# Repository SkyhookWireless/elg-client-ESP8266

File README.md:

# elg-client-demo
ELG Client Demo Space

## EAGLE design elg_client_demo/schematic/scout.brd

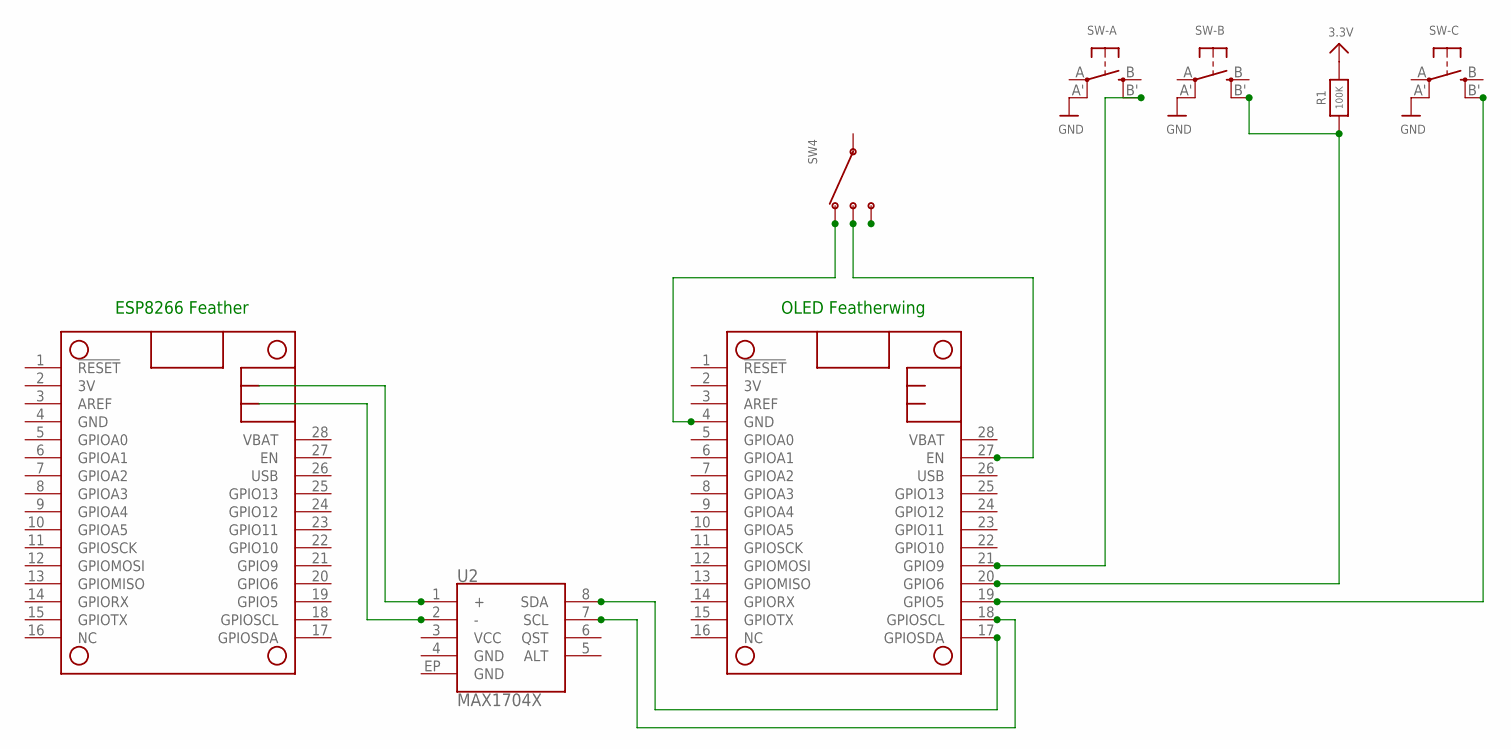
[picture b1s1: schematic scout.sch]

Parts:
MS1, MS2: MICROBUILDER_FEATHERWING_NODIM; MICROBUILDER_FEATHERWING_DIM
R1: 100K; MICROBUILDER_0603-MINI
SW4: CSS-1310TB; JSM07011
SW-A: MICROBUILDER_SWITCH_TACT_SMTKMT0; MICROBUILDER_BTN_KMT0
SW-B: MICROBUILDER_SWITCH_TACT_SMTKMT0; MICROBUILDER_BTN_KMT0
SW-C: MICROBUILDER_SWITCH_TACT_SMTKMT0; MICROBUILDER_BTN_KMT0
U2: MAX1704X; SPARKFUN_TDFN-8

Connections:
3.3V: R1.2
GND: MS2.4 (GND), SW-A.A' (P1), SW-B.A' (P1), SW-C.A' (P1)
unnamed: MS1.21 (GPIO9), SW-A.B' (S1)
unnamed: MS1.20 (GPIO6), R1.1, SW-B.B' (S1)
unnamed: MS1.19 (GPIO5), SW-C.B' (S1)
unnamed: MS1.4 (GND), SW4.4 (3)
unnamed: MS1.27 (EN), SW4.2
unnamed: MS1.17 (GPIOSDA), U2.8 (SDA)
unnamed: MS1.18 (GPIOSCL), U2.7 (SCL)

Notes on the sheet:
ESP8266 Feather
OLED Featherwing

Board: 2 copper layers, 8 parts (0 on the bottom side), 8 nets, no tracks yet.

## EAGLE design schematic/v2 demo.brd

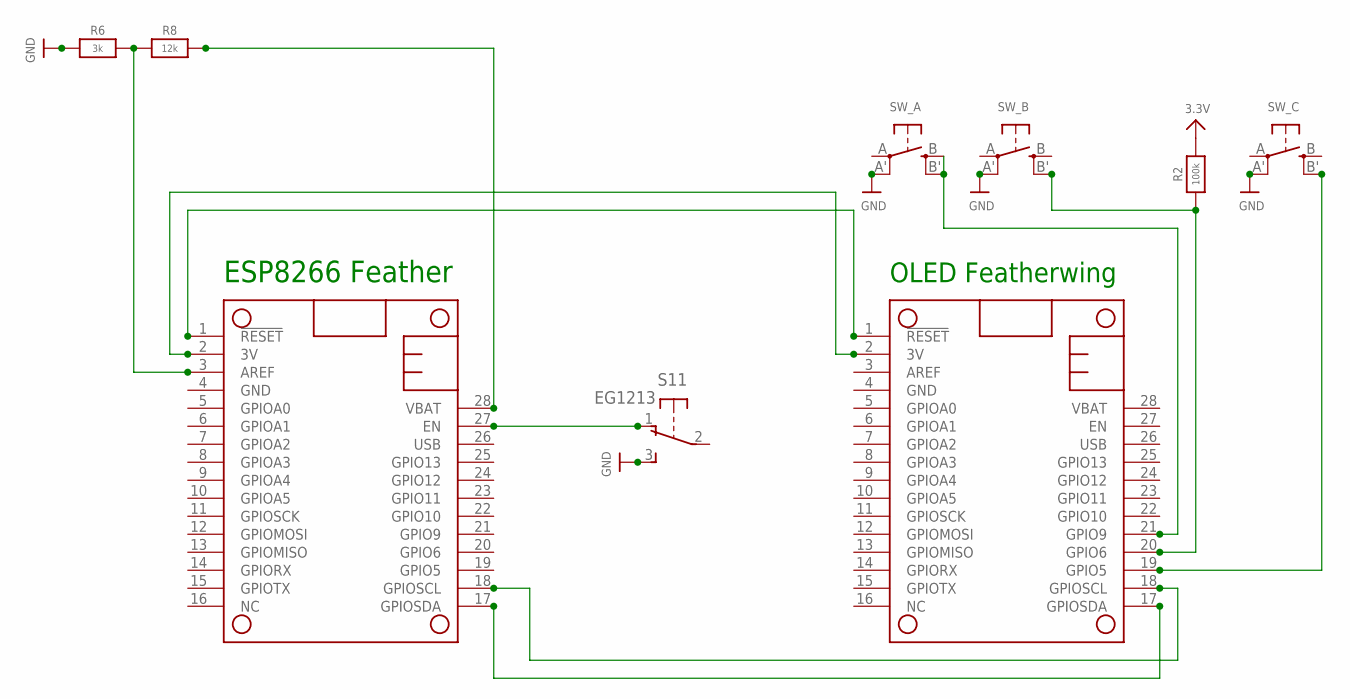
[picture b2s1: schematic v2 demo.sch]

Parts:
MS1: FEATHERWING
MS2: FEATHERWING_NODIM; FEATHERWING_DIM
R2: 100k; MICROBUILDER_0603-MINI
R6: 3k; MICROBUILDER_0603-MINI
R8: 12k; MICROBUILDER_0603-MINI
S1: EG1213
SW_A: MICROBUILDER_SWITCH_TACT_SMTKMT0; MICROBUILDER_BTN_KMT0
SW_B: MICROBUILDER_SWITCH_TACT_SMTKMT0; MICROBUILDER_BTN_KMT0
SW_C: MICROBUILDER_SWITCH_TACT_SMTKMT0; MICROBUILDER_BTN_KMT0

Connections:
3.3V: R2.2
3V: MS1.2 (3V), MS2.2 (3V)
GND: MS1.4 (GND), MS2.4 (GND), R6.1, S1.3 (S), SW_A.A' (P1), SW_B.A' (P1), SW_C.A' (P1)
unnamed: MS2.21 (GPIO9), SW_A.B (S), SW_A.B' (S1)
unnamed: MS2.20 (GPIO6), R2.1, SW_B.B' (S1)
unnamed: MS1.18 (GPIOSCL), MS2.18 (GPIOSCL)
unnamed: MS1.17 (GPIOSDA), MS2.17 (GPIOSDA)
unnamed: MS1.1 (!RESET), MS2.1 (!RESET)
unnamed: MS2.19 (GPIO5), SW_C.B' (S1)
unnamed: MS1.3 (AREF), R6.2, R8.1
unnamed: MS1.27 (EN), S1.1 (O)
VBAT: MS1.28 (VBAT), R8.2

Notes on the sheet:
ESP8266 Feather
OLED Featherwing

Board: 2 copper layers, 14 parts (3 on the bottom side), 11 nets, no tracks yet.

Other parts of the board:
FRAME1: FRAME-LETTER; CREATIVE_COMMONS
U$4: FEATHERLOGO
U$8: ADAFRUIT_5MM
U$14: PCBFEAT-REV-040
U$16: ADAFRUIT_3.5MM

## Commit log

2016-06-02 POST AP change
2016-06-03 network storage as JSON implemented but not tested
2016-06-06 added handleScan and improved wifi connect
2016-06-07 added css dependencies and began designing web interface
2016-06-07 small html page to change ssid, added umbrella js for ajax calls and doc manipulation
2016-06-07 added skyhook logo to main landing page
2016-06-09 added more web interface
2016-06-13 frontend changes, wifi connect breaking on no_ssid
2016-06-21 client mode
2016-07-01 preferences toggles
2016-07-04 all features implemented
2016-07-05 skyhook logo and repurposed setConnected in OLED library
2016-07-05 comments in cpp added
2016-07-05 authors updated
2016-07-06 added MAX_AUTOJOINS_APS
2016-07-06 removed not needed graphics library
2016-07-10 debugging and wifi connection updated
2016-07-11 landing page update
2016-07-11 corrected table
2016-07-11 display initial startup
2016-07-11 wrong display mode
2016-07-11 switch buttons
2016-07-11 switch inital state to CLNT
2016-07-11 commented config
2016-07-12 added show IP in AP
2016-07-12 Location error handling
2016-07-12 corrected AES key to original
2016-07-12 IP printout updated
2016-07-13 fix truncation
2016-07-13 wrap text
2016-07-13 moved files
2016-07-13 moved files back
2016-07-13 truncating fixed
2016-07-13 updated header files
2016-07-13 removed submodule
2016-07-14 fixed web location
2016-07-14 testing
2016-07-14 removed all submodules
2016-07-14 reactive sub
2016-07-14 switch to dev ELG-Client2
2016-07-14 updated to new ELG-Client Code
2016-07-14 backtrack timestamp
2016-07-14 added timestamp
2016-07-14 timestamp fixed
2016-07-14 HPE display on web client fixed
2016-07-18 debugging
2016-07-20 Changed location error message on OLED
2016-07-20 reverted to voltage, fixed table
2016-07-20 fixed location json
2016-07-21 location timeout fixed
2016-07-29 merging with scout
2016-07-29 merging
2016-07-29 updated data
2016-07-29 battery low indicator
2016-08-02 AP_STA -> AP
2016-08-08 libraries readded
2016-08-09 updated client default start, switched from AP -> AP_STA
2016-08-11 fixed wrong userid crash and SPIFFS malfunction on router disconnect
2016-08-11 changed back to correct user id
2016-08-15 deleted branch
2016-08-15 reverted
2016-08-17 upgraded to v2 protocol: untested
2016-08-17 v2 protocol GPS coor working
2016-08-19 working v2 upgrade
2016-08-19 ELG-Common Submodule
2016-08-19 fixed changing to AP mode during wifi diconnect overwrites IP address
2016-09-19 Update ELG-Common to the 'common' directory and update the common files to the latest of V2.
2016-09-23 Add a script to automatically do the manual merge from 'elg_client_demo/common' to 'elg_client_demo'.
2016-09-26 Add comments and usage of script merge_common_to_sketch.sh.
2016-11-14 Update to the protocol to support multi-cell-types
2016-11-16 [EC-30] Newly assembled Demo devices are in a cyclic reset.
2016-11-17 WiFi.disconnect() is only called when being connected already
2016-11-21 EC-32] Need capability for demo device to roam between networks
    Fix:
    1. Code clean up;
    2. Reconnect to known WiFi in loop().
2016-11-29 [EC-27] Print timestamp for every location response on console port
2016-11-29 Format index.html by online HTML formatter
2016-11-29 [EC-34] Create webpage on demo board to configure realm_id and aes_key
2016-11-29 [EC-35] Fix Arduino code transformation script
2016-11-30 [EC-39] Load realm_id and aes_key in json on ESP8266 at bootup instead of hardcoded in source code
    Fix:
    1. In index.html, use the default 'preference' values upon webpage reloading, instead of setting them explicitly;
    2. Remove the hardcoded realm_id and aes_key from config.h;
    3. Load realm_id and aes_key from the json configuration file;
    4. Remove unnecessary sky_util.h.
2016-11-30 Add realm_id and aes_key in preferences.json
2016-11-30 [EC-40] ESP8266 infinite loop in connecting WiFi
2016-11-30 Reorganize code base to make it more readable
2016-12-07 [EC-44] Raise limit on scanned APs from 50 to 100
2016-12-07 Do not display the content of realm_id and aes_key in webpage
2016-12-08 Fix typos
2016-12-09 Strip off AP mode and let esp8266 work on client only mode
2016-12-09 [EC-45] Relabel realmID to partnerId in demo device Web Page
2016-12-09 Additional fix for [EC-40] to make it easy to respond to button interrupt
2016-12-13 Scan hidden networks as well
2016-12-14 [EC-46] Partner_ID and aes_key need to be reentered if there are changes made on Systems Panel
2016-12-14 [EC-49] Cannot reset WiFi connection when the WiFi password is lost
2017-01-04 [ELG-170] Scout Demo device for Verizon disconnects after an hour
    Fix:
    1. Add yield() everything the system calls may take time;
    2. Forcefully reset ESP8266 every 1000 requests being handled.
2017-01-06 Fix ESP reset issue
2017-01-06 [EC-42] Create cleaner client interface to Skyhook functionality
2017-09-07 [EC-53] Demo Devices hanging on 'Connected to...' Screen
2017-10-18 Remove ESP reset and multiplicative factors according to code review comments

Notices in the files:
parts and their libraries:
SparkFun-Aesthetics: Licensing: Creative Commons ShareAlike 4.0 International - https://creativecommons.org/licenses/by-sa/4.0
SparkFun-Aesthetics: Released under the Creative Commons Attribution Share-Alike 4.0 License
SparkFun-Aesthetics: https://creativecommons.org/licenses/by-sa/4.0
